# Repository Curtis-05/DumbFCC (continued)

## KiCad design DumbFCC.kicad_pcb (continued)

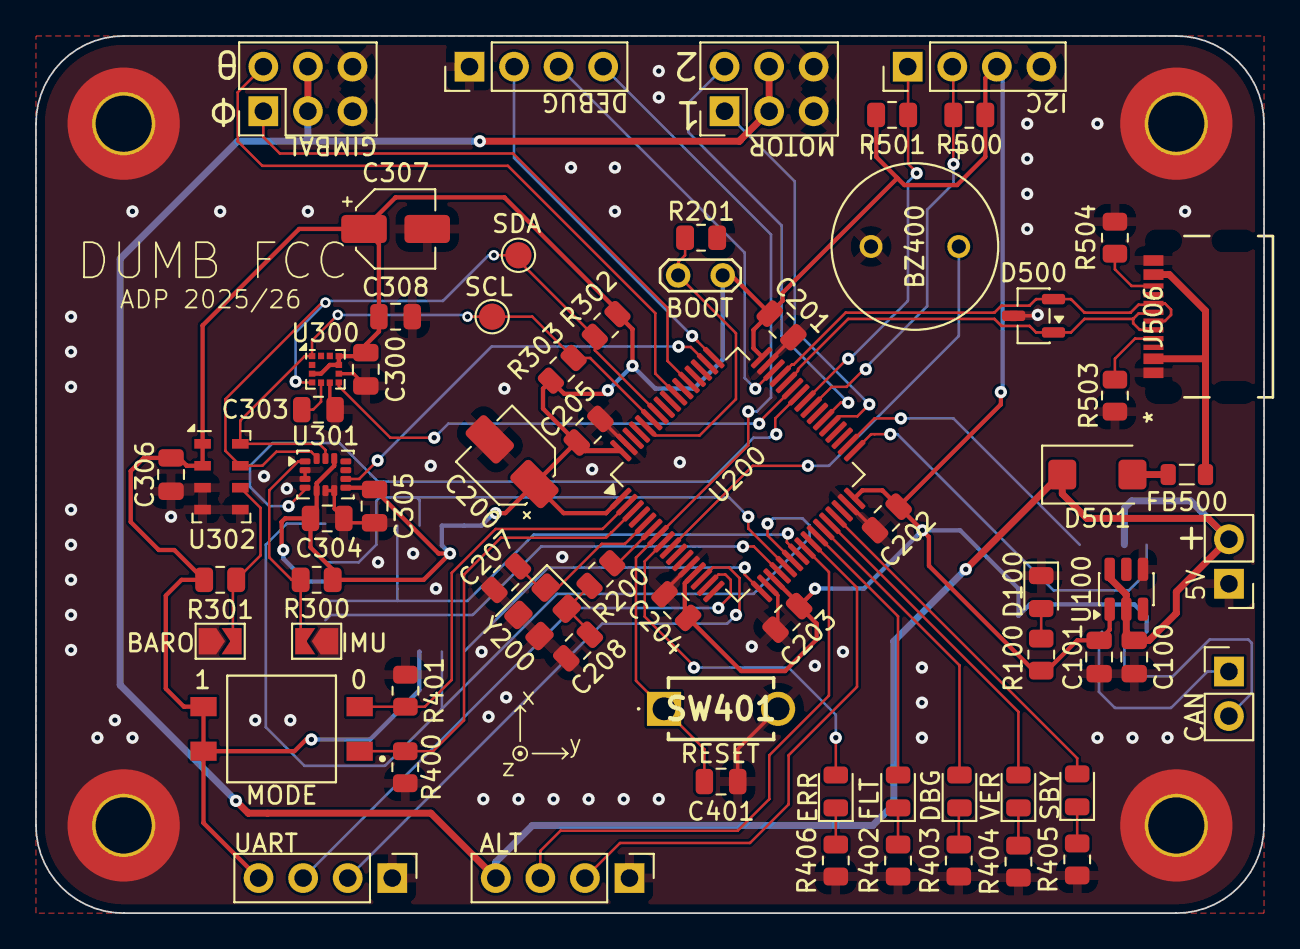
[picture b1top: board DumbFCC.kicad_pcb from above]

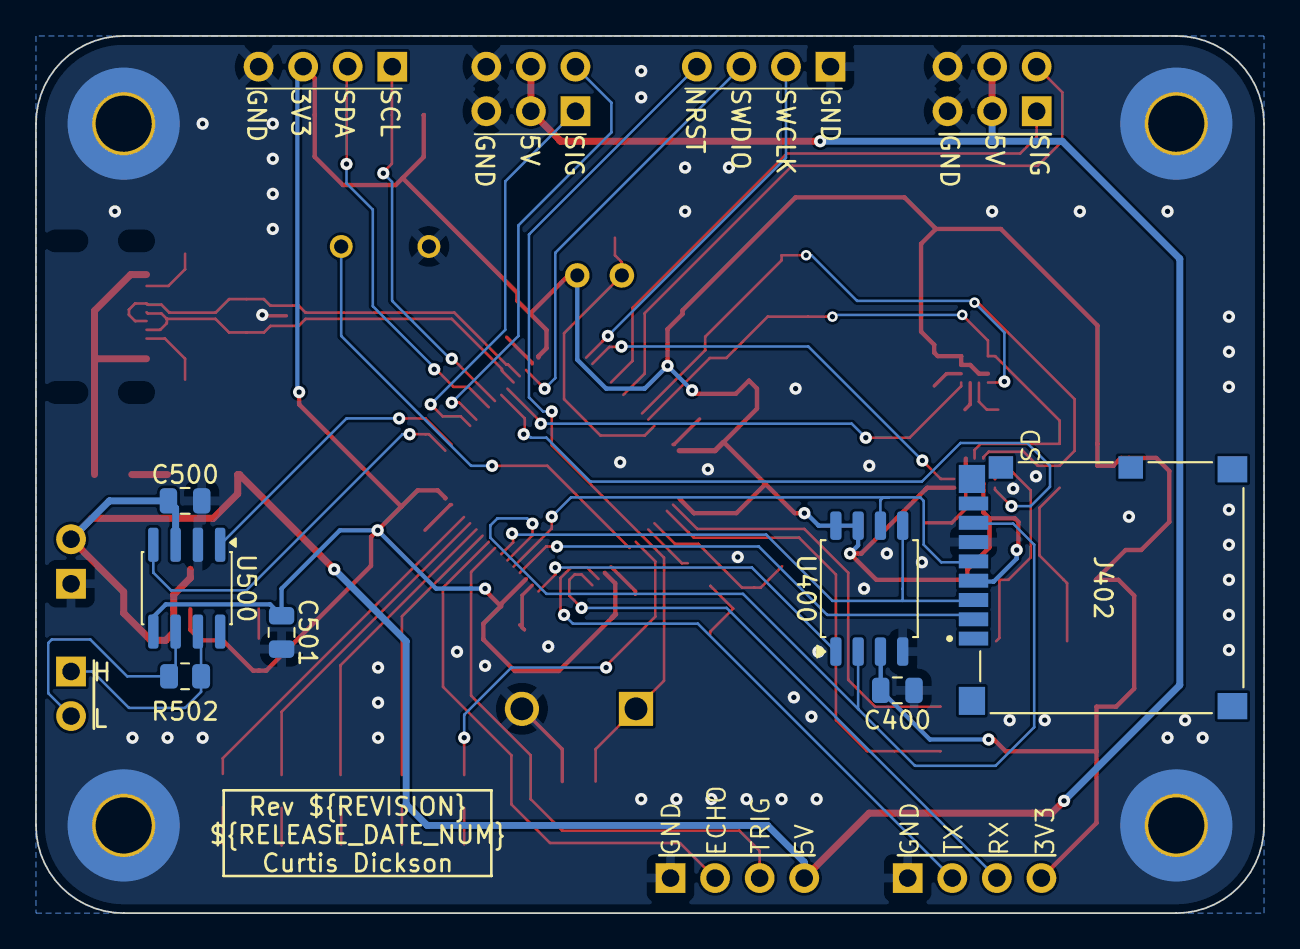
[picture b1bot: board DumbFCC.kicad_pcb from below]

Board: 4 copper layers, 70.0 x 50.0 mm, 79 parts (7 on the bottom side), 57 nets.

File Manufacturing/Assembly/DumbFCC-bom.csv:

Row,Quantity Per PCB,References,Value,Datasheet,Footprint,Description,Manufacturer,Manufacturer Part Number,Supplier Part Number
1,1,BZ400,Buzzer,~,XDCR_AI-1027-TWT-3V-R,"Buzzer, polarized",,,
2,2,C207 C208,10p,~,C_0805_2012Metric,Unpolarized capacitor,,,
3,14,C201 C202 C203 C204 C205 C300 C304 C305 C306 C308 C400 C401 C500 C501,100n,~,C_0805_2012Metric,Unpolarized capacitor,,,
4,1,C303,220n,~,C_0805_2012Metric,Unpolarized capacitor,,,
5,2,C100 C101,470n,~,C_0805_2012Metric,Unpolarized capacitor,,,
6,2,C200 C307,10u,~,CP_Elec_4x5.7,Polarized capacitor,,,
7,1,D401,DBG,~,LED_0805_2012Metric,Light emitting diode,,,
8,1,D501,D_Schottky,~,P25_DO-214AC_SMA,Schottky diode,,,
9,1,D404,ERR,~,LED_0805_2012Metric,Light emitting diode,,,
10,1,D500,ESDA6V1l-tp,https://www.st.com/resource/en/datasheet/esdal.pdf,SOT-23-3,"TVS Diode Array, 5.5V Standoff, 2 Channels, SOT23",,,
11,1,D400,FLT,~,LED_0805_2012Metric,Light emitting diode,,,
12,1,D100,PWR,~,LED_0805_2012Metric,Light emitting diode,,,
13,1,D403,SBY,~,LED_0805_2012Metric,Light emitting diode,,,
14,1,D402,VER,~,LED_0805_2012Metric,Light emitting diode,,,
15,1,FB500,FerriteBead,~,L_0805_2012Metric,Ferrite bead,,,
16,8,J100 J300 J500 J501 J502 J503 J504 J505,5V Input,~,PinHeader_1x02_P2.54mm_Vertical,"Generic connector, single row, 01x02, script generated Generic connector, single row, 01x04, script generated Generic connector, double row, 02x03, counter clockwise pin numbering scheme (similar to DIP package numbering), script generated (kicad-library-utils/schlib/autogen/connector/)",,,
17,1,J402,SD port,,MOLEX_5027740891,,,,
18,1,J506,USB C,https://www.molex.com/en-us/products/part-detail-pdf/2171790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,2171790001_MOL,,,,
19,1,R502,120,~,R_0805_2012Metric,Resistor,,,
20,6,R100 R402 R403 R404 R405 R406,330,~,R_0805_2012Metric,Resistor,,,
21,1,R200,620,~,R_0805_2012Metric,Resistor,,,
22,2,R503 R504,5k1,~,R_0805_2012Metric,Resistor,,,
23,9,R201 R300 R301 R302 R303 R400 R401 R500 R501,10k,~,R_0805_2012Metric,Resistor,,,
24,1,SW400,Mode Switch,~,SW_DS04-254-1-02BK-SMT,"2x DIP Switch, Single Pole Single Throw (SPST) switch, small symbol",,,
25,1,SW401,Reset,~,DTS32NVB,"Push button switch, generic, two pins",,,
26,1,U100,ADP3330ARTZ3.3-RL7,,SOT-23-6,,,,
27,1,U300,LIS2MDL,https://www.st.com/resource/en/datasheet/lis2mdl.pdf,LGA-12_2x2mm_P0.5mm,"Ultra-low-power, 3-axis digital output magnetometer, LGA-12",,,
28,1,U301,LSM6DSL,https://www.st.com/resource/en/datasheet/lsm6dsl.pdf,LGA-14_3x2.5mm_P0.5mm_LayoutBorder3x4y,"I2C/SPI, iNEMO inertial module: always-on 3D accelerometer and 3D gyroscope, 1.71V to 3.6V VCC",,,
29,1,U500,MCP2562T-E_SN,https://www.snapeda.com/parts/MCP2562T-E/SN/Microchip/datasheet/,SOIC-8_3.9x4.9mm_P1.27mm,,Microchip,,
30,1,U302,MS5607-02BA,https://www.te.com/commerce/DocumentDelivery/DDEController?A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,LGA-8_3x5mm_P1.25mm,"Barometric pressure sensor, 20cm resolution, 10 to 1200 mbar, I2C and SPI interface up to 20MHz, LGA-8",,,
31,1,U400,SST26VF064BT-104I/SM,http://ww1.microchip.com/downloads/en/DeviceDoc/20005045C.pdf,SOIC-8_5.3x5.3mm_P1.27mm,"8-Mbit, 2.7 to 3.6V, SPI Flash Memory, SOIC-8",,,
32,1,U200,STM32H573RIT6,https://www.st.com/resource/en/datasheet/stm32h573ri.pdf,LQFP-64_10x10mm_P0.5mm,"STMicroelectronics Arm Cortex-M33 MCU, 2048KB flash, 640KB RAM, 250 MHz, 1.62-3.6V, 49 GPIO, LQFP64",,,
33,1,Y200,25MHz,~,Crystal_SMD_Abracon_ABM8G-4Pin_3.2x2.5mm,"Four pin crystal, GND on pins 2 and 3",,,

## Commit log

2026-03-13 First draft of schematic
2026-03-13 Fixed issue where Altium_Theme was missing
2026-03-13 Update Outputs
2026-03-13 preliminary version of PCB layout
2026-03-13 Checked version of schematic and PCB
2026-03-13 Resolved ERC errors
2026-03-13 Update CHANGELOG
2026-03-13 Update Outputs (release)
2026-03-13 [PCB][Fixed] Fixed wrong Diode footprint and Changed TVS diode package, also changed wrong footprint of CAN transiever chip. [Changed] Changed the FLASH chip to a different model due to a stocking is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
2026-03-14 [pcb][changed] updated footprints that were incorrect, changed flash memory module due to stock issues
